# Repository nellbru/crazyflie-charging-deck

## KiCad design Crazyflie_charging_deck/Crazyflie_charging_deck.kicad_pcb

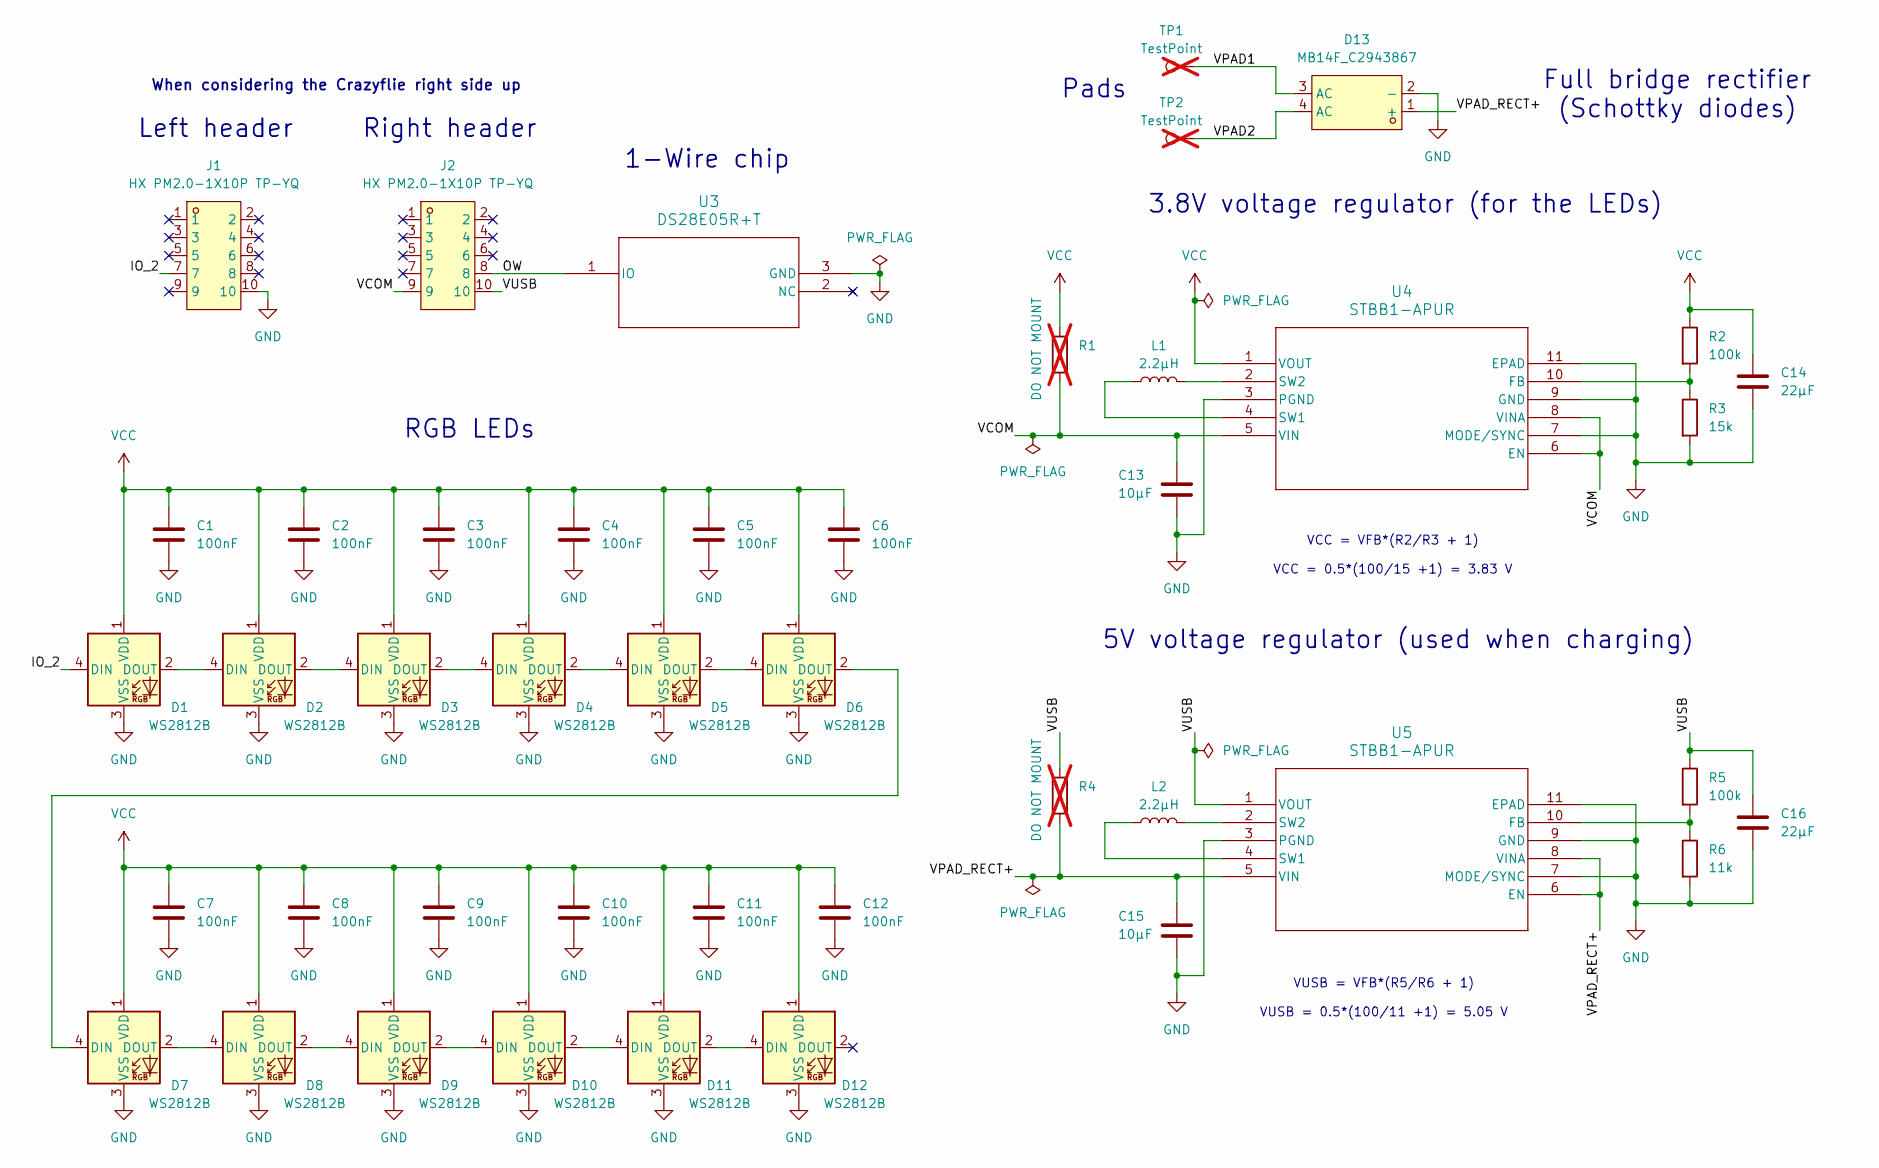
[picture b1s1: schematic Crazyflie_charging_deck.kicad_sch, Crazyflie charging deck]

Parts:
C1, C2, C3, C4, C5, C6, C7, C8, C9, C10, C11, C12: 100nF; C_0603_1608Metric; LCSC Part C14663
C13, C15: 10µF; C_1206_3216Metric; LCSC Part C13585
C14, C16: 22µF; C_1206_3216Metric; LCSC Part C12891
D1, D2, D3, D4, D5, D6, D7, D8, D9, D10, D11, D12: WS2812B; LED_WS2812B_PLCC4_5.0x5.0mm_P3.2mm; LCSC Part C2874885
D13: MB14F_C2943867; MBF-SMD_L4.7-W3.8-P2.50-LS7.0-BL; MPN MB14F; LCSC Part C2943867
J1, J2: HX PM2.0-1X10P TP-YQ; CONN-SMD_10P-P2.00_TPYE-1_SMD-10P; MPN HX PM2.0-1x10P TP-YQ; LCSC Part C42379209
L1, L2: 2.2µH; L_Sunlord_SWPA4020S; LCSC Part C83423
R1, R4: DO NOT MOUNT; R_0603_1608Metric; not fitted
R2, R5: 100k; R_0603_1608Metric; LCSC Part C25803
R3: 15k; R_0603_1608Metric; LCSC Part C22809
R6: 11k; R_0603_1608Metric; LCSC Part C25950
TP1, TP2: TestPoint; TestPoint_Pad_4.0x4.0mm; not fitted
U3: DS28E05R+T; LCSC Part C2064942
U4, U5: STBB1-APUR; LCSC Part C967636

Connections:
/IO_2: D1.4 (DIN), J1.7
/OW: J2.8, U3.1 (IO)
/VCOM: C13.1, J2.9, R1.2, U4.5 (VIN), U4.6 (EN), U4.8 (VINA)
/VPAD1: D13.3 (AC), TP1.1 (1_1)
/VPAD2: D13.4 (AC), TP2.1 (1_1)
/VPAD_RECT+: C15.1, D13.1 (+), R4.2, U5.5 (VIN), U5.6 (EN), U5.8 (VINA)
/VUSB: C16.1, J2.10, R4.1, R5.1, U5.1 (VOUT)
GND: C1.2, C2.2, C3.2, C4.2, C5.2, C6.2, C7.2, C8.2, C9.2, C10.2, C11.2, C12.2, C13.2, C14.2, C15.2, C16.2, D1.3 (VSS), D2.3 (VSS), D3.3 (VSS), D4.3 (VSS), D5.3 (VSS), D6.3 (VSS), D7.3 (VSS), D8.3 (VSS), D9.3 (VSS), D10.3 (VSS), D11.3 (VSS), D12.3 (VSS), D13.2 (-), J1.10, R3.2, R6.2, U3.3 (GND), U4.3 (PGND), U4.7 (MODE/SYNC), U4.9 (GND), U4.11 (EPAD), U5.3 (PGND), U5.7 (MODE/SYNC), U5.9 (GND), U5.11 (EPAD)
unnamed: D1.2 (DOUT), D2.4 (DIN)
unnamed: D2.2 (DOUT), D3.4 (DIN)
unnamed: D3.2 (DOUT), D4.4 (DIN)
unnamed: D4.2 (DOUT), D5.4 (DIN)
unnamed: D5.2 (DOUT), D6.4 (DIN)
unnamed: D6.2 (DOUT), D7.4 (DIN)
unnamed: D7.2 (DOUT), D8.4 (DIN)
unnamed: D8.2 (DOUT), D9.4 (DIN)
unnamed: D9.2 (DOUT), D10.4 (DIN)
unnamed: D10.2 (DOUT), D11.4 (DIN)
unnamed: D11.2 (DOUT), D12.4 (DIN)
unnamed: R2.2, R3.1, U4.10 (FB)
unnamed: L1.1, U4.4 (SW1)
unnamed: L1.2, U4.2 (SW2)
unnamed: R5.2, R6.1, U5.10 (FB)
unnamed: L2.1, U5.4 (SW1)
unnamed: L2.2, U5.2 (SW2)
VCC: C1.1, C2.1, C3.1, C4.1, C5.1, C6.1, C7.1, C8.1, C9.1, C10.1, C11.1, C12.1, C14.1, D1.1 (VDD), D2.1 (VDD), D3.1 (VDD), D4.1 (VDD), D5.1 (VDD), D6.1 (VDD), D7.1 (VDD), D8.1 (VDD), D9.1 (VDD), D10.1 (VDD), D11.1 (VDD), D12.1 (VDD), R1.1, R2.1, U4.1 (VOUT)

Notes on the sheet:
VCC = VFB*(R2/R3 + 1) VCC = 0.5*(100/15 +1) = 3.83 V
VUSB = VFB*(R5/R6 + 1) VUSB = 0.5*(100/11 +1) = 5.05 V
5V voltage regulator (used when charging)
When considering the Crazyflie right side up
RGB LEDs
Right header
Left header
Pads
Full bridge rectifier (Schottky diodes)
1-Wire chip
3.8V voltage regulator (for the LEDs)

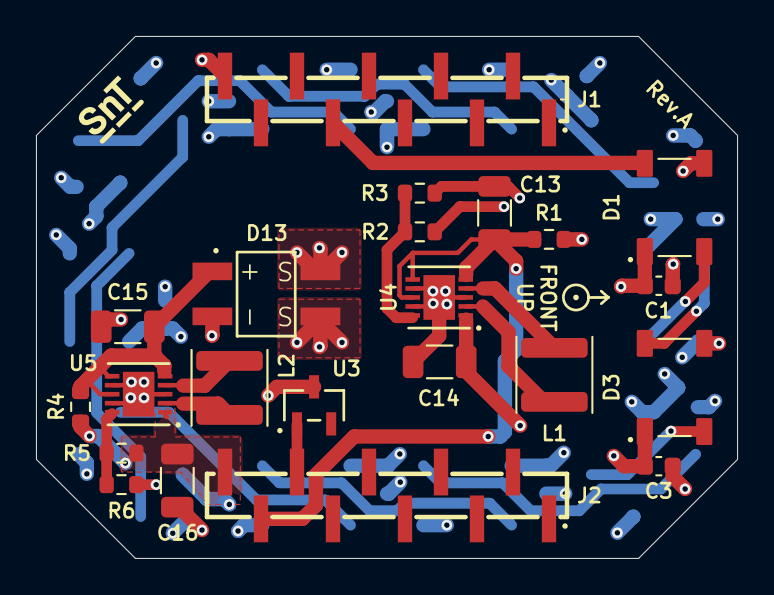
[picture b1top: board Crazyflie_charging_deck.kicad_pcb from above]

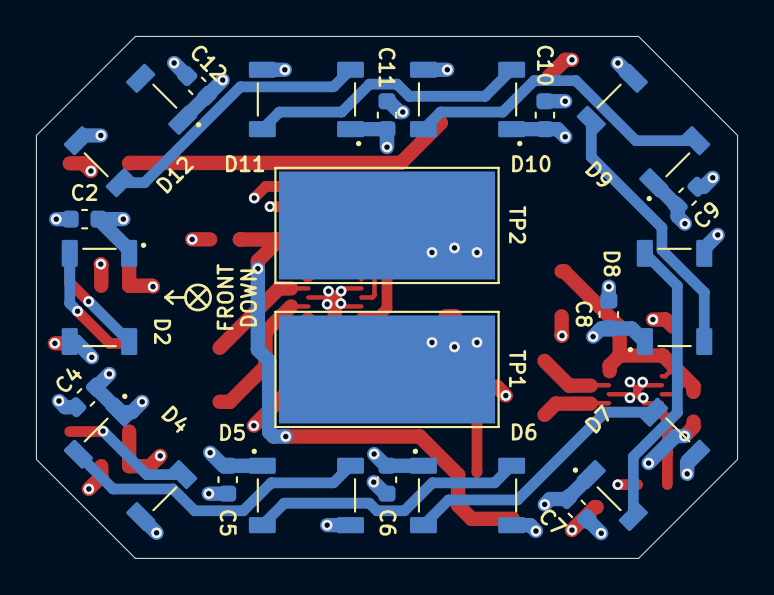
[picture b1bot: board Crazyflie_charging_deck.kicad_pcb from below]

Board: 4 copper layers, 38.9 x 29.0 mm, 45 parts (22 on the bottom side), 26 nets.

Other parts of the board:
EXP_ORIENTATION: VAL**; CF_orientation

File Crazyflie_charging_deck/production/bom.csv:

Designator,Footprint,Quantity,Value,LCSC Part #
"C1, C10, C11, C12, C2, C3, C4, C5, C6, C7, C8, C9",0603,12,100nF,C14663
"C13, C15",1206,2,10µF,C13585
"C14, C16",1206,2,22µF,C12891
"D1, D10, D11, D12, D2, D3, D4, D5, D6, D7, D8, D9",LED_WS2812B_PLCC4_5.0x5.0mm_P3.2mm,12,WS2812B,C2874885
D13,MBF-SMD_L4.7-W3.8-P2.50-LS7.0-BL,1,MB14F_C2943867,C2943867
"J1, J2",CONN-SMD_10P-P2.00_TPYE-1_SMD-10P,2,HX PM2.0-1X10P TP-YQ,C42379209
"L1, L2",L_Sunlord_SWPA4020S,2,2.2µH,C83423
"R2, R5",0603,2,100k,C25803
R3,0603,1,15k,C22809
R6,0603,1,11k,C25950
U3,DS28E05R+T,1,DS28E05R+T,C2064942
"U4, U5",STBB1-APUR,2,STBB1-APUR,C967636
